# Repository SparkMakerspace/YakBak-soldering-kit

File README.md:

---
layout: page
title: YakSpark Soldering Kit
permalink: /index.html
---

## About
This project is intended to act as a short introduction to soldering, as well as to act as a platform for exploring audio inputs/outputs with Arduino.

## Components
* Seeed Studio XIAO ESP32C3 ([source](https://www.seeedstudio.com/Seeed-XIAO-ESP32C3-p-5431.html))
* Electret Microphone Amp Module (or clone)
* Adafruit 2130 - PAM8302 (or clone)
* 10Ω resistor (THT)
* 100nf ceramic capacitor
* 8Ω 0.5W Speaker ([source](https://www.harfington.com/products/p-1077007?currency=USD&variant=42125198622969&utm_medium=cpc&utm_source=google&utm_campaign=Google%20Shopping&srsltid=AfAwrE5xj9HOdhrmCOGlX5rFUivPkEOZYhoFlpFoKg4NeLDqNTXnyzFJOVI))

## Assembly

## PCB
The PCB for this project was designed in KiCAD 7.

## Code
Download this repository and open the [software](https://github.com/SparkMakerspace/YakBak-soldering-kit/tree/main/software/test%20software) directory to find the firmware source. The firmware is intended to be modified and flashed with [PlatformIO](https://platformio.org/).

## Enclosure
The YakSpark enclosure is intended to be 3D printed and was designed in FreeCAD. Source, STEP, and STL files are found in the [enclosure](https://github.com/SparkMakerspace/YakBak-soldering-kit/tree/main/enclosure) directory.

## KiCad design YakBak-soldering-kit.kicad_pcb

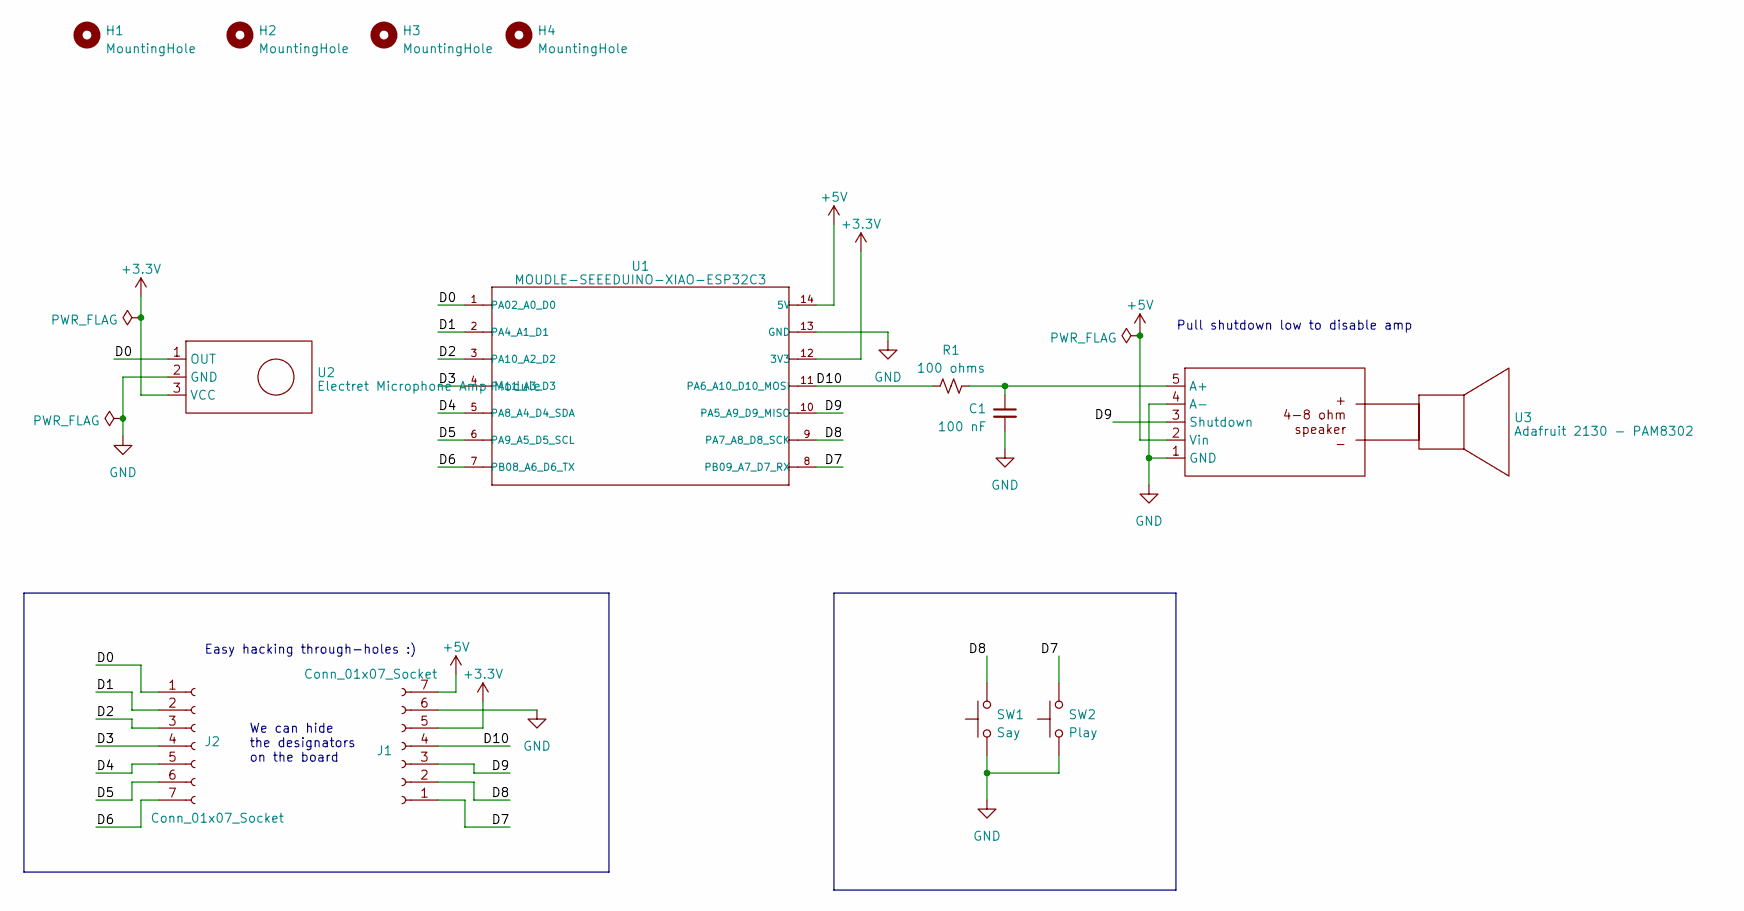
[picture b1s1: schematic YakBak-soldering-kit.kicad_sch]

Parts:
C1: 100 nF; C_Disc_D5.1mm_W3.2mm_P5.00mm
H1, H2, H3, H4: MountingHole; MountingHole_2.5mm
J1, J2: Conn_01x07_Socket; PinSocket_1x07_P2.54mm_Vertical
R1: 100 ohms; R_Axial_DIN0204_L3.6mm_D1.6mm_P7.62mm_Horizontal
SW1: Say; SW_PUSH_6mm
SW2: Play; SW_PUSH_6mm
U1: MOUDLE-SEEEDUINO-XIAO-ESP32C3; MOUDLE14P-SMD-2.54-21X17.8MM
U2: Electret Microphone Amp Module; PinSocket_1x03_P2.54mm_Vertical
U3: Adafruit 2130 - PAM8302; PinHeader_1x05_P2.54mm_Vertical

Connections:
+3.3V: J1.5, U1.12 (3V3), U2.3 (VCC)
+5V: J1.7, U1.14 (5V), U3.2 (Vin)
/D0: J2.1, U1.1 (PA02_A0_D0), U2.1 (OUT)
/D1: J2.2, U1.2 (PA4_A1_D1)
/D2: J2.3, U1.3 (PA10_A2_D2)
/D3: J2.4, U1.4 (PA11_A3_D3)
/D4: J2.5, U1.5 (PA8_A4_D4_SDA)
/D5: J2.6, U1.6 (PA9_A5_D5_SCL)
/D6: J2.7, U1.7 (PB08_A6_D6_TX)
/D7: J1.1, SW2.2, U1.8 (PB09_A7_D7_RX)
/D8: J1.2, SW1.2, U1.9 (PA7_A8_D8_SCK)
/D9: J1.3, U1.10 (PA5_A9_D9_MISO), U3.3 (Shutdown)
/D10: J1.4, R1.1, U1.11 (PA6_A10_D10_MOSI)
GND: C1.2, J1.6, SW1.1, SW2.1, U1.13 (GND), U2.2 (GND), U3.1 (GND), U3.4 (A-)
unnamed: C1.1, R1.2, U3.5 (A+)

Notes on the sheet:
We can hide the designators on the board
Pull shutdown low to disable amp
Easy hacking through-holes :)

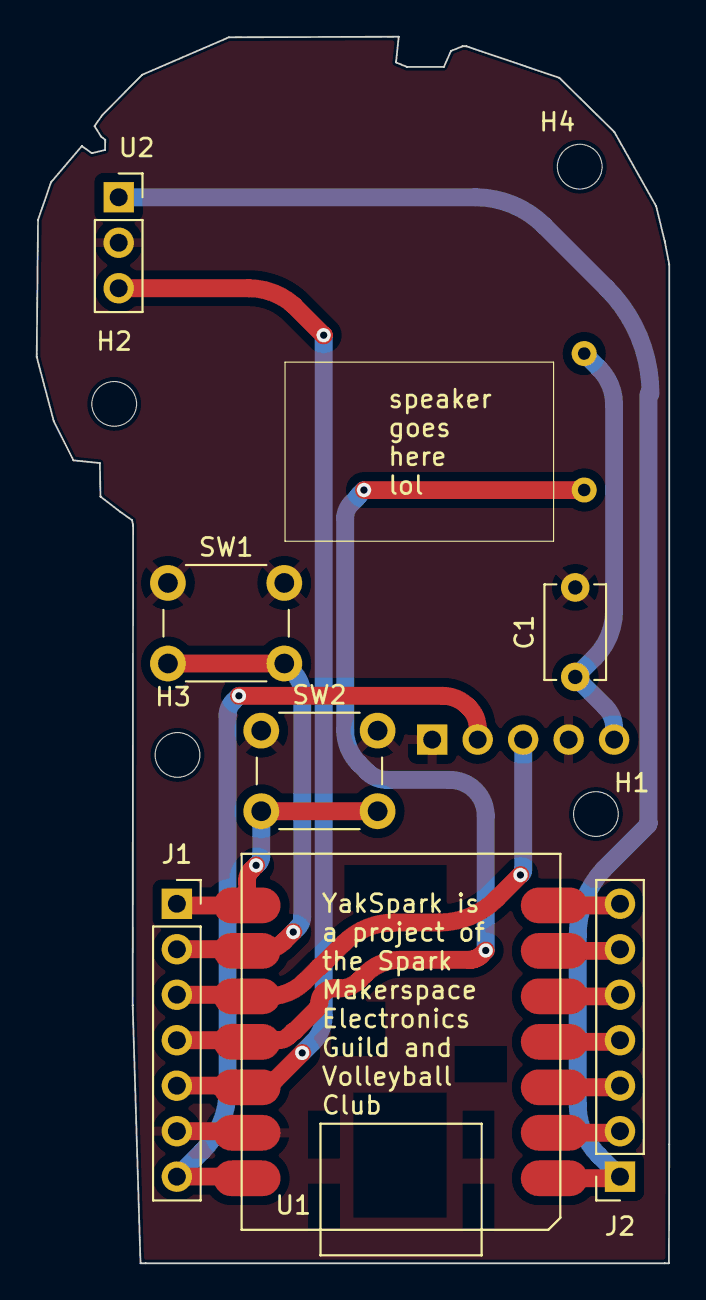
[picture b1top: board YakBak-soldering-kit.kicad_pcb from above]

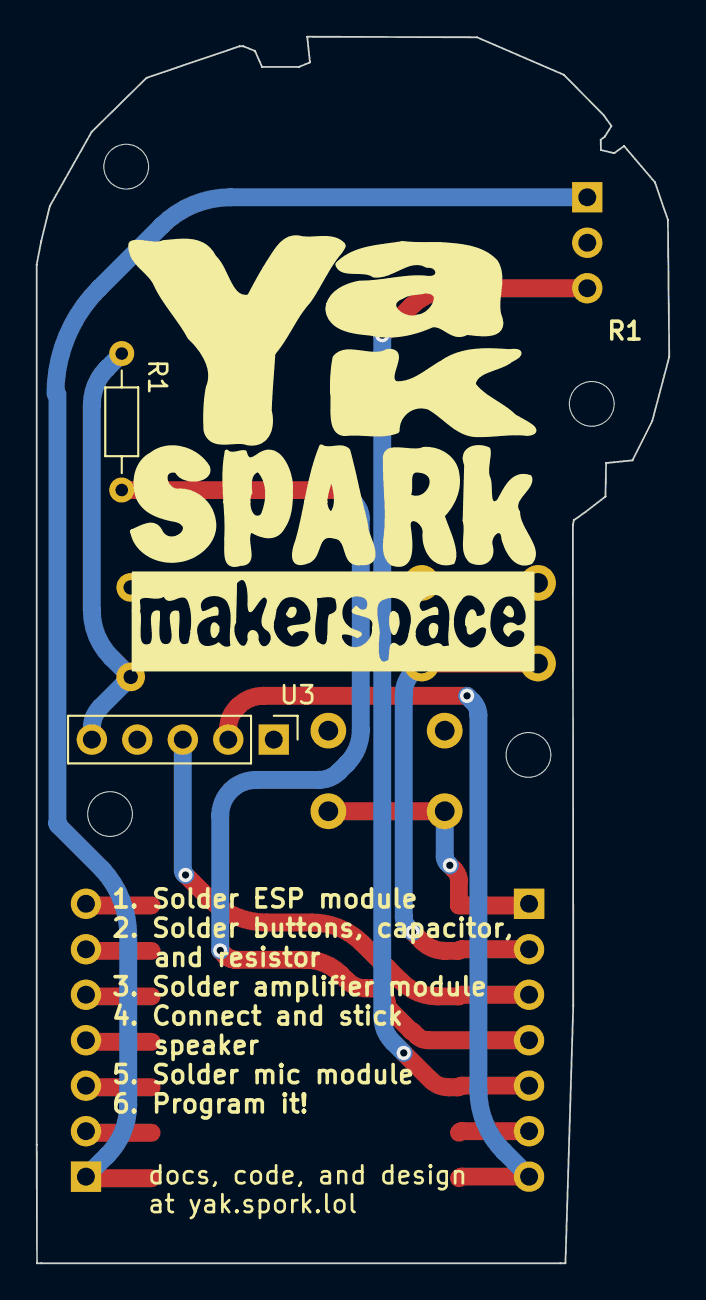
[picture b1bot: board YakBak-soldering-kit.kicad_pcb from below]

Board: 2 copper layers, 35.3 x 68.5 mm, 13 parts (2 on the bottom side), 15 nets.

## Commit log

2023-04-09 Finished the schematic. Review time!
2023-04-10 changes to schematic to fix ERC check and addition of PCB edges.
2023-04-11 finished draft layout and updated missing symbols/footprints
2023-04-14 added artwork and routed traces
2023-04-14 add ground fill to F.Cu
2023-04-14 cleaned up, rounded traces, added directions
2023-04-14 plot gerber files for R1
2023-04-14 set grid origin for PCB.
2023-04-21 Enclosure 3D files
    This file has the freecad files, step files, and gcode for printing the Yak Spark Enclosure. The gcode has not been tested, use at your own risk.
2023-04-23 Updates to fix interference
    Removed an interference, modified record button to have slightly larger symbol
2023-04-25 Updates from 4/24 meeting
2023-04-27 add STL files, since Cura doesn't seem to support STEP models.
2023-04-29 Mechanical connection updates
2023-05-01 updated the stl exports
2023-05-01 initialized PIO project for testing
2023-05-02 Made a pdf of the schematic and started a test program
2023-05-04 latest changes
2023-05-05 more progress
2023-05-05 heck - pressing say causes bad stuff
2023-05-06 Yay it works!
2023-05-06 Oh hey now SPIFFS should auto format once
2023-05-06 minor tweak
2023-05-06 add STL files of enclosure
2023-05-06 add images pcb and enclosure
2023-05-06 rename enclosure folder
2023-05-06 cleanup move of enclosure folder
2023-05-06 rename software folder
2023-05-06 add README
2023-05-06 add jekyll config
2023-05-06 missing ruby configs for jekyll
2023-05-06 Added photos and assembly instructions
